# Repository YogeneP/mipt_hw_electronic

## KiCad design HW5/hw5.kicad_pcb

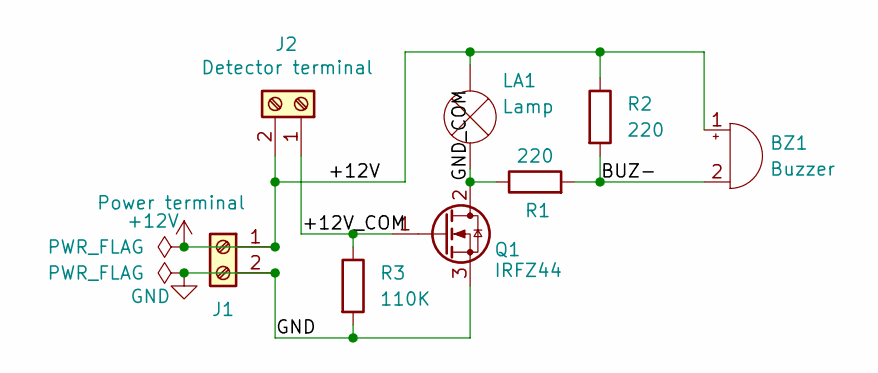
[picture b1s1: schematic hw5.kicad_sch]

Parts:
BZ1: Buzzer; Buzzer_12x9.5RM7.6
J1: Power terminal; TerminalBlock_RND_205-00287_1x02_P5.08mm_Horizontal
J2: Detector terminal; TerminalBlock_RND_205-00287_1x02_P5.08mm_Horizontal
LA1: Lamp; TerminalBlock_RND_205-00287_1x02_P5.08mm_Horizontal
Q1: IRFZ44; TO-220-3_Vertical
R1, R2: 220; R_Axial_DIN0207_L6.3mm_D2.5mm_P10.16mm_Horizontal
R3: 110К; R_Axial_DIN0207_L6.3mm_D2.5mm_P10.16mm_Horizontal

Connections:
+12V: BZ1.1 (+), J1.1, J2.2, LA1.2 (+), R2.1
/+12V_COM: J2.1, Q1.1 (G), R3.1
/BUZ-: BZ1.2 (-), R1.2, R2.2
/GND_COM: LA1.1 (-), Q1.2 (D), R1.1
GND: J1.2, Q1.3 (S), R3.2

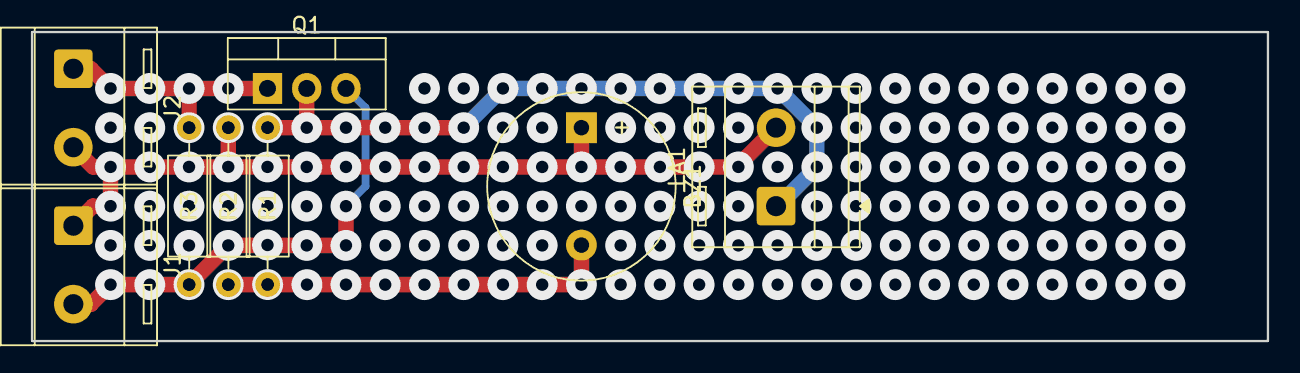
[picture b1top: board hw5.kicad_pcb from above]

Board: 2 copper layers, 80.0 x 20.0 mm, 8 parts (0 on the bottom side), 5 nets.
